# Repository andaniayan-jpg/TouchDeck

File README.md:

# TouchDeck

A macropad with touch sensor

Touchdeck is a macropad with touch sensitive display, it has no keys. 

## Table of Contents

WHAT IS TOUCHDECK
WHAT MAKES IT UNIQUE
FEATURES
HOW TO USE IT
BILL OF MATERIALS
SCHEMATIC OVERVIEW
PCB details
3D design 
Assembly Guide
Firmware

---

## What is TouchDeck?

TouchDeck is a device made with ESP32 as the MCU, it acts a touch pad making it both a macropad and a scribble pad. It has 2 modes.

**1.  Macropad Mode**
The screen acts like a touchpad, which digital keys visible on the screen, it enables the device to act as a Touch Screen MacroPad.

**2. Scribble Pad Mode**
When switched to Scribble pad mode, it shows a plain white canvas that can be used to take notes, doodle and etc. NOTHING IS SAVED PERMANENTLY, ONCE EXITING THIS MODE, REMOVES ALL THE WORK. 
---

## What Makes It Unique

It is unique because it doesnt use any buttons or keys like ordinary macropad, it has touch screen. It is unique because it acts as both macropad and scribble pad.
It has a customised PCB, LED, buzzer and  etc.
---

## Main Features

- ESP32-S3 based custom PCB
- 3.5 inch SPI TFT touchscreen display
- XPT2046 touch controller
- USB-C power and data
- On-screen macro buttons
- Temporary scribble/doodle mode
- Back and clear controls
- USB HID keyboard shortcut output
- WS2812B RGB status LED
- Buzzer feedback

---

## How to Use It

### 1. Power the Device

Connect the device with the laptop or PC. Turn on with power switch, RGB LED turns on and shows the status.

### 2. Select the mode, Macropad or scribble. 

When powered on, the screen shows two main options:

- **MacroPad Mode**
- **ScribblePad Mode**

Tap the mode you want to use.

### 3. MacroPad Mode

The touchscreen shows several shortcut buttons. When a button is touched, the ESP32-S3 sends a keyboard shortcut to the connected laptop via USB HID.

You can add, remove, increase and reduce the sizes of buttons according to your choice by changing the firmware, as it is a custom PCB!!!

### 4. ScribblePad Mode

The screen becomes a temporary drawing area. You can write with your finger or a capacitive stylus, doodle quick ideas, sketch small layouts, or scribble notes while thinking.

The drawing is **not saved** — it is purely temporary.

- **Clear** — removes the drawing from the screen
- **Back** — returns to the home screen and clears the canvas

---

## Bill of Materials (BOM)

visit "" for BOM. 

> 
## Component connections
   for component connections, refer to the schematic image or go through the schematic source file to view exact connections. 

## Assembly Guide
   All the components used are present in the folder `cad_assembly` in STEP/STP format, for 3D model, Enclousre, and 3D parts  overview, go through that folder.

### Tools needed
-Soldering iron and flux
-Tweezers
-USB-C data cable

---
### Step 1 — Solder the Small Components

Let's start by soldering the tiny parts. First, apply some flux to the pads where the resistors and capacitors will go. Carefully position each component in place and solder them down. Since resistors and capacitors are the smallest parts, it's easier to tackle these first.

### Step 2 — Solder the USB-C Connector 

Next up is the USB-C connector. Begin by putting a little solder on the ground pads in the center of the PCB. Align the USB-C connector so all the pins match up with the pads. Tack down one corner to hold it in place, then double-check everything’s aligned before soldering the rest. Finally, solder the 5V and ground shield tabs — these will need a bit more heat to get a good connection.

### Step 3 — Solder the Voltage Regulator and ESD IC

Time to solder the voltage regulator and ESD IC. Start with the AP2112K (U2) in its SOT-23-5 package. Just make sure to pay attention to the orientation according to the silkscreen. After that, move on to the USBLC6-2SC6 (U3) in its SOT-23-6 package, keeping an eye on the pin 1 indicator.

### Step 4 — Solder the Transistor and Buzzer

For the next step, solder the transistor (Q1), which is the 2N3904 in the SOT-23 footprint. Then, insert the passive buzzer (LS1) into the through-hole, making sure the positive marking aligns with the pad label. Solder it from the bottom.

### Step 5 — Solder the WS2812B LED (U4)

Next, let’s work on the WS2812B LED, which has an integrated controller. First, apply a bit of flux to all four pads. Solder one of the corner pads first, then work on the others. Just a tip: try not to apply heat for too long on each pad.

### Step 6 — Solder the Push Buttons

Moving on, place the push buttons (SW1 for Boot and SW2 for Reset) into their through-holes. Insert them from the top and then solder their four legs from the bottom.

### Step 7 — Solder the ESP32-S3-WROOM-1 Module

This is one of the most important parts of the project. Start by applying flux on all the pads on three sides of the module footprint. Carefully position the module, ensuring the edges align with the PCB pads. Tack down two corner pads to secure it, then solder each pad using a drag-soldering method or solder wick. Make sure to check under a magnifying glass to spot any solder bridges.

Remember: **Do not solder the antenna area.** The module has a PCB antenna, so keep that section clear.

### Step 8 — Solder the Display Connector (J2)

Now, insert the 1×14 female header into J2. If you’re not using a header, you can solder wires directly instead. Solder all 14 pins from the bottom.

### Step 9 — Power-On Test (Before Display)

Before connecting the display, let's check if the power is working. Connect a USB-C cable from the board to your computer. Use a multimeter to measure the voltage between the 3.3V test point and ground. You should see a reading between **3.28–3.35V**. If it’s 0V or over 3.4V, disconnect immediately and check the solder joints on U2 and C1/C2.

### Step 10 — Attach the Display Module

Now it’s time to add the 3.5" ILI9488 display module into J2. Be careful to check the pin 1 orientation — there’s a marking on the silkscreen to help you out. If you’re doing a permanent build, you might want to use a little hot glue or double-sided foam tape to hold the display flat against the PCB.

### Step 11 — Mount Everything in the Enclosure

Finally, position the PCB in the bottom of the enclosure, making sure the mounting holes line up with the standoff posts. Insert the M2.5 × 6mm standoffs from below through the PCB holes. Then, place the enclosure top frame over the display and secure it with M2.5 × 4mm screws on both the top and bottom. 

And that’s it! At this point, you should have everything nicely assembled and ready to go.

---

---

Hardware design files are released under CERN Open Hardware Licence v2 (CERN-OHL-S).
Firmware source code is released under MIT License.
See `LICENSE` for full terms.

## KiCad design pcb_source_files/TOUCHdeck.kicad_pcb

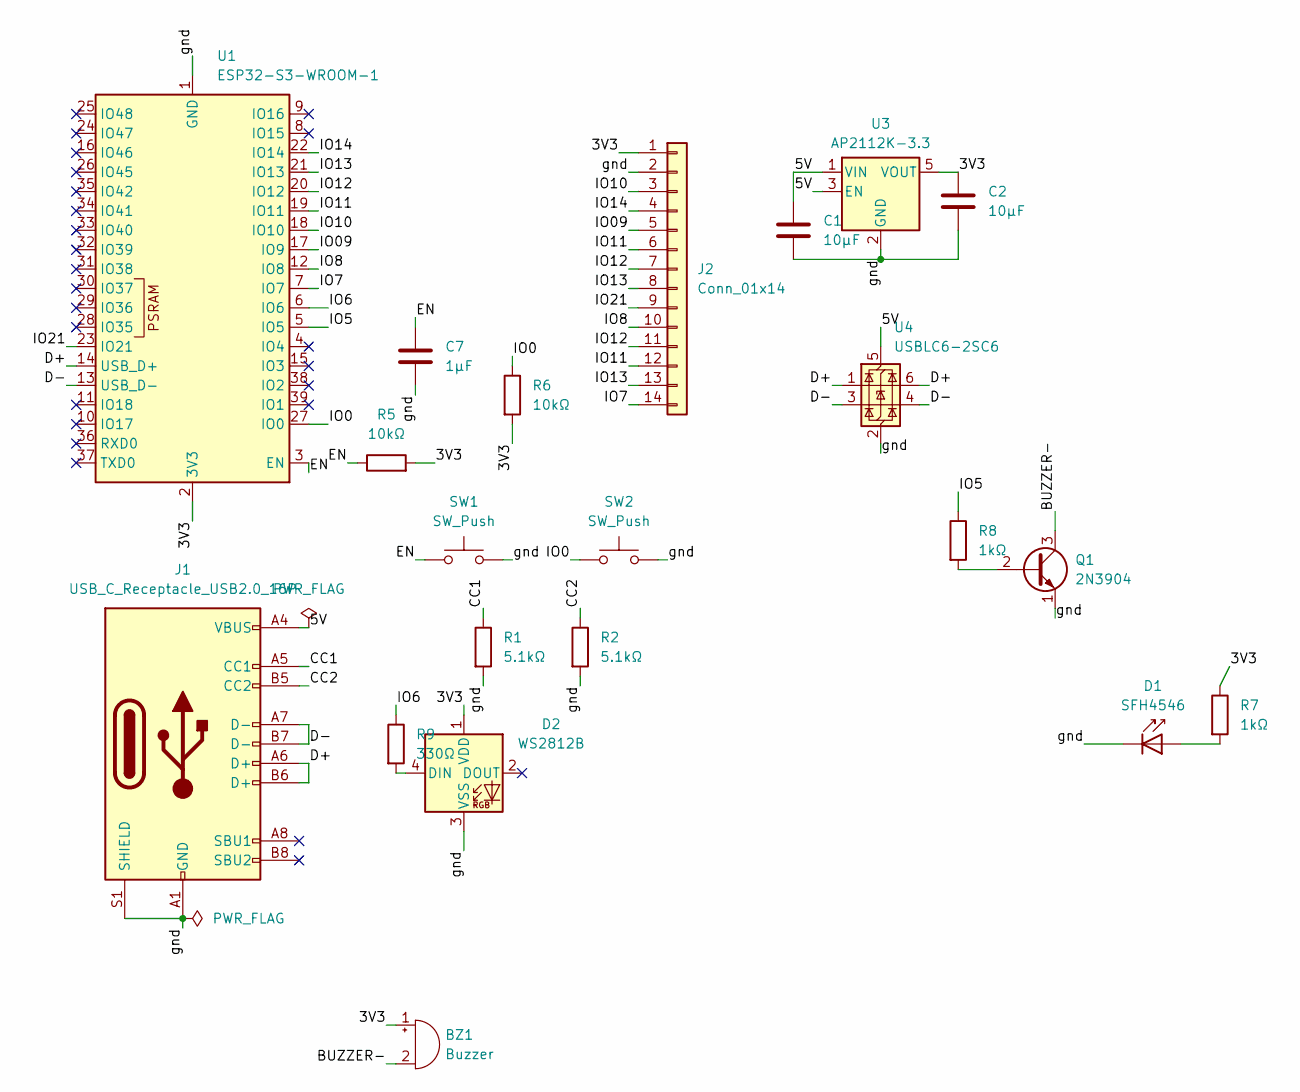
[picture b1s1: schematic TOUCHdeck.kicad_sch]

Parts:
BZ1: Buzzer; Buzzer_12x9.5RM7.6
C1, C2: 10μF; C_0805_2012Metric
C7: 1μF; C_0805_2012Metric
D1: SFH4546; LED_D5.0mm
D2: WS2812B; LED_WS2812B_PLCC4_5.0x5.0mm_P3.2mm
J1: USB_C_Receptacle_USB2.0_16P; USB_C_Receptacle_HCTL_HC-TYPE-C-16P-01A
J2: Conn_01x14; PinHeader_1x14_P2.54mm_Vertical
Q1: 2N3904; TO-92_Inline
R1, R2: 5.1kΩ; R_0603_1608Metric
R5, R6: 10kΩ; R_0603_1608Metric
R7, R8: 1kΩ; R_0603_1608Metric
R9: 330Ω; R_0603_1608Metric
SW1, SW2: SW_Push; SW_PUSH_6mm
U1: ESP32-S3-WROOM-1
U3: AP2112K-3.3; SOT-23-5
U4: USBLC6-2SC6; SOT-23-6

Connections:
/3V3: BZ1.1 (+), C2.2, D2.1 (VDD), J2.1 (VCC), R5.2, R6.2, R7.1, U1.2 (3V3), U3.5 (VOUT)
/5V: C1.1, J1.A4 (VBUS), J1.A9 (VBUS), J1.B4 (VBUS), J1.B9 (VBUS), U3.1 (VIN), U3.3 (EN), U4.5 (VBUS)
/BUZZER-: BZ1.2 (-), Q1.3 (C)
/CC1: J1.A5 (CC1), R1.1
/CC2: J1.B5 (CC2), R2.1
/D+: J1.A6 (D+), J1.B6 (D+), U1.14 (USB_D+), U4.1 (I/O1), U4.6 (I/O1)
/D-: J1.A7 (D-), J1.B7 (D-), U1.13 (USB_D-), U4.3 (I/O2), U4.4 (I/O2)
/EN: C7.1, R5.1, SW1.1, U1.3 (EN)
/IO0: R6.1, SW2.1, U1.27 (IO0)
/IO5: R8.1, U1.5 (IO5)
/IO6: R9.1, U1.6 (IO6)
/IO7: J2.14 (TOUCH_IRQ), U1.7 (IO7)
/IO8: J2.10 (TOUCH_CS), U1.12 (IO8)
/IO09: J2.5 (LCD_DC), U1.17 (IO9)
/IO10: J2.3 (LCD_CS), U1.18 (IO10)
/IO11: J2.6 (LCD_MOSI), J2.12 (TOUCH_DIN), U1.19 (IO11)
/IO12: J2.7 (LCD_SCK), J2.11 (TOUCH_CLK), U1.20 (IO12)
/IO13: J2.8 (LCK_MISO), J2.13 (TOUCH_DO), U1.21 (IO13)
/IO14: J2.4 (LCD_RST), U1.22 (IO14)
/IO21: J2.9 (LCD_BL), U1.23 (IO21)
/gnd: C1.2, C2.1, C7.2, D1.1 (K), D2.3 (VSS), J1.A1 (GND), J1.A12 (GND), J1.B1 (GND), J1.B12 (GND), J1.S1 (SHIELD), J2.2 (GND), Q1.1 (E), R1.2, R2.2, SW1.2, SW2.2, U1.1 (GND), U1.40 (GND), U1.41 (GND), U3.2 (GND), U4.2 (GND)
unnamed: D1.2 (A), R7.2
unnamed: D2.4 (DIN), R9.2
unnamed: Q1.2 (B), R8.2

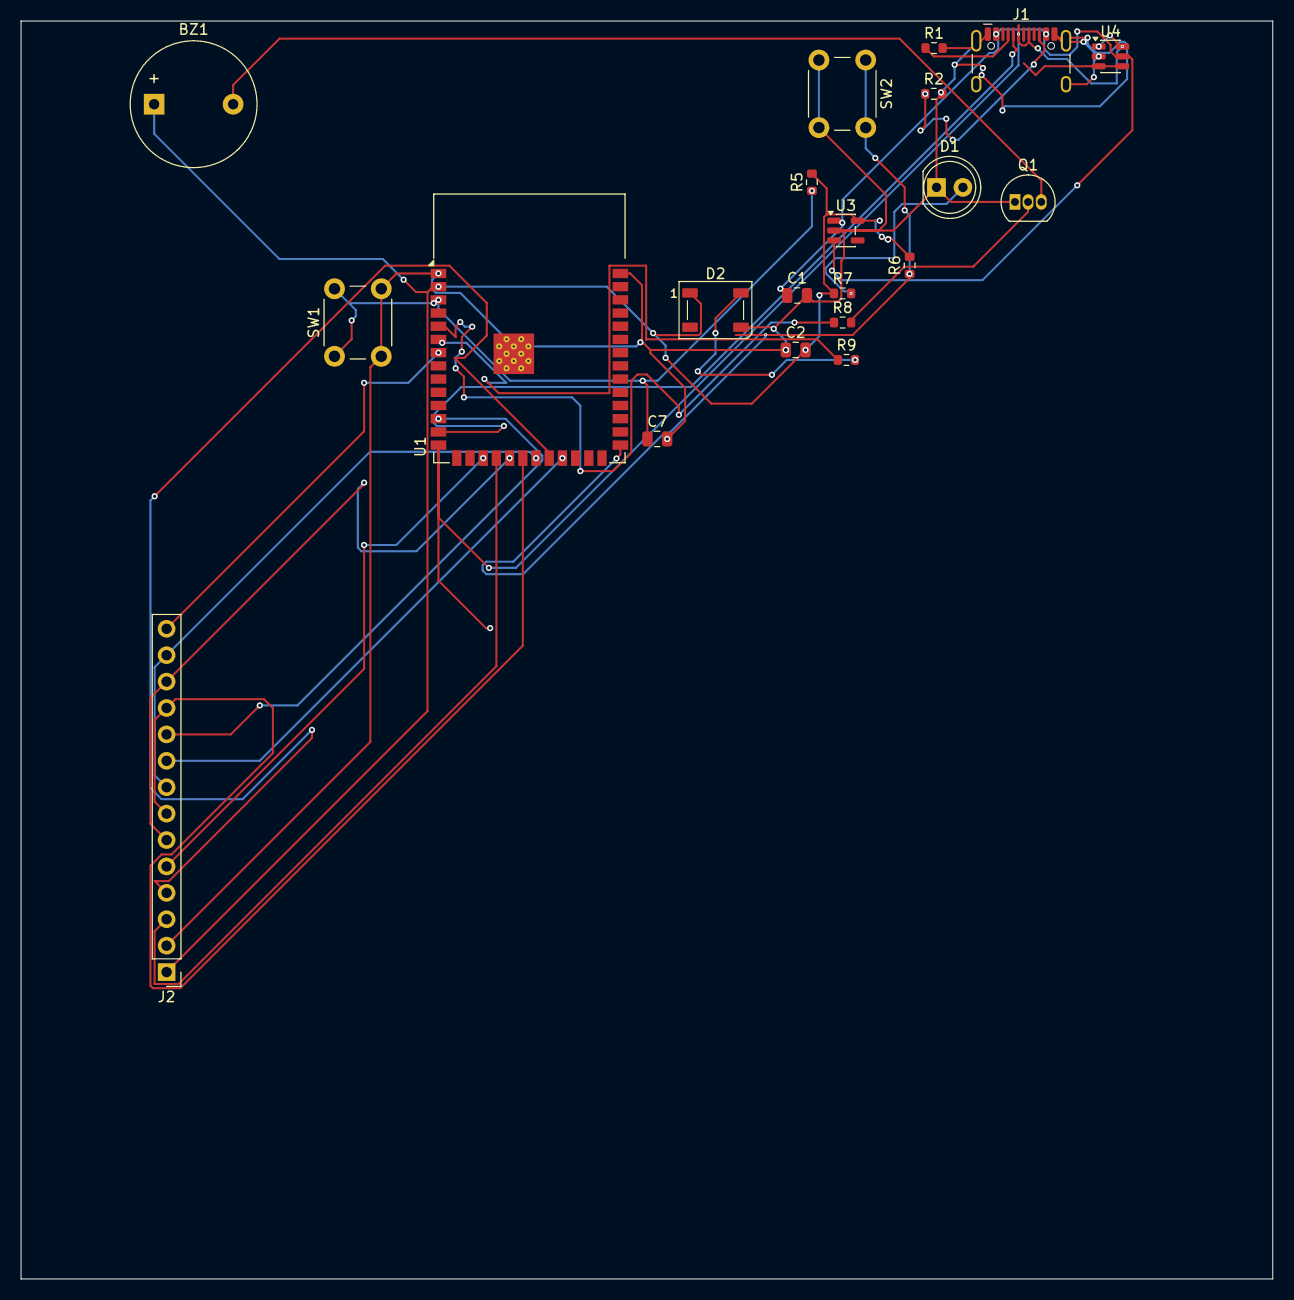
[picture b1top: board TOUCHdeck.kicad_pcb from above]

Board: 2 copper layers, 120.4 x 121.0 mm, 21 parts (0 on the bottom side), 24 nets.

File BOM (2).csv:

Reference,Qty,Component,Value/Part,Footprint,Source,Link,Notes
U1,1,MCU Module,ESP32-S3-WROOM-1-N8R8,ESP32-S3-WROOM-1,Espressif / Robu,https://www.espressif.com/en/module/esp32-s3-wroom-1-en,Main ESP32-S3 module with native USB HID capability for macropad output
Q1,1,NPN Transistor,2N3904,TO-92_Inline,LCSC,https://www.lcsc.com/product-detail/C118538.html,Buzzer driver transistor
D1,1,LED,SFH4546 5mm IR LED,LED_D5.0mm,DigiKey / ams OSRAM,https://www.digikey.in/en/products/detail/ams-osram-usa-inc/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,Indicator/LED footprint from PCB export; verify this is the intended LED before ordering
"R6,R5",2,Resistor,10k? 0603,R_0603_1608Metric,LCSC,https://www.lcsc.com/product-detail/C269701.html,EN/BOOT pull-up resistors
"R8,R7",2,Resistor,1k? 0603,R_0603_1608Metric,LCSC,https://www.lcsc.com/product-detail/C22548.html,Buzzer transistor base resistor and power LED/current-limit resistor
"SW2,SW1",2,Push Button,6x6mm tactile push button,SW_PUSH_6mm,LCSC,https://www.lcsc.com/product-detail/C393938.html,BOOT and RESET buttons
U3,1,Voltage Regulator,AP2112K-3.3,SOT-23-5,LCSC,https://www.lcsc.com/product-detail/C23380830.html,3.3V LDO regulator from USB 5V
R9,1,Resistor,330 0603,R_0603_1608Metric,LCSC,https://www.lcsc.com/product-detail/C23138.html,Series resistor for WS2812B data line
BZ1,1,Buzzer,12mm through-hole active buzzer,Buzzer_12x9.5RM7.6,LCSC,https://www.lcsc.com/product-detail/C360615.html,Touch feedback buzzer; footprint Buzzer_12x9.5RM7.6
"C1,C2",2,Capacitor,10µF 0805 ceramic capacitor,C_0805_2012Metric,LCSC,https://www.lcsc.com/product-detail/C89827.html,AP2112K regulator input/output capacitors
"R1,R2",2,Resistor,5.1k?,R_0603_1608Metric,LCSC,https://www.lcsc.com/product-detail/C105580.html,USB-C CC1/CC2 pull-down resistors
U4,1,USB ESD Protection,USBLC6-2SC6,SOT-23-6,LCSC / STMicroelectronics,https://www.lcsc.com/product-detail/C2827654.html,ESD protection for USB D+ and D- lines
D2,1,Addressable RGB LED,WS2812B-B/W SMD5050-4P,LED_WS2812B_PLCC4_5.0x5.0mm_P3.2mm,LCSC,https://www.lcsc.com/product-detail/C114586.html,Mode/status RGB LED
J2,1,Display Connector,1x14 2.54mm vertical header,PinHeader_1x14_P2.54mm_Vertical,KiCad standard footprint / generic electronics supplier,https://www.lcsc.com/category/568.html,Connector footprint for external 3.5 inch SPI TFT touch display module
J1,1,USB-C Receptacle,HCTL HC-TYPE-C-16P-01A,USB_C_Receptacle_HCTL_HC-TYPE-C-16P-01A,LCSC / JLCPCB,https://www.lcsc.com/product-detail/C2894897.html,USB-C power/programming/HID connection
C7,1,Capacitor,1µF 0805 ceramic capacitor,C_0805_2012Metric,LCSC,https://www.lcsc.com/product-detail/C91186.html,EN/reset stability capacitor
PCB1,1,Custom PCB,TouchDeck / ScribbleDeck PCB,Gerber-manufactured PCB,JLCPCB / PCBWay,https://github.com/andaniayan-jpg/TouchDeck/blob/ea78aa653e2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,Main printed circuit board manufactured from Gerber files; PCB itself is included as a BOM item
DISP1,1,Touch Display Module,3.5 inch SPI TFT LCD ILI9488 + XPT2046 touch module,External module connected through J2 1x14 header,Robokits / electronics supplier,https://robokits.co.in/displays/lcd-display/spi-tft-3.5-lcd-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,Main touchscreen used for macro buttons and temporary scribble pad
CASE1,1,Enclosure,Custom 3D printed TouchDeck enclosure,3D printed part,Self-printed / 3D printing service,CAD/TouchDeck_enclosure.step,Outer case for touchscreen device
CABLE1,1,USB-C Cable,USB-C data/power cable,External cable,Amazon / electronics supplier,https://www.amazon.in/Type-C-Data-Cable/s?k=Type-C+Data+Cable,"Used for power, programming, and USB HID connection to laptop"
MECH1,1,Mounting Hardware,M2.5 hex screws,Mechanical hardware,Amazon / hardware supplier,https://www.amazon.in/binifiMux-190pcs-Socket-Assortment-Sta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,Used to fasten the PCB/enclosure parts

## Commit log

2026-05-12 Create m
2026-05-12 Create firmware
2026-05-13 Enhance README with additional images
    Added images to enhance the README documentation and provide visual context for the TouchDeck project.
2026-05-25 Wrote the readme by myself
    Updated the README.md to clarify features, usage instructions, and assembly steps for the TouchDeck device myself.
